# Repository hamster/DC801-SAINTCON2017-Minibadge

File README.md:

# DC801-SAINTCON2017-Minibadge
Minibadge design for the 2017 SAINTCON badge with a DC801 theme

Powered

Front

Back

The Minibadge includes a spiffy DC801 design and two automatic slow-cycling RGB LEDs

The Minibadge can be used in two ways:

1. SAINTCON Minibadge Mode
2. Shirt Pin Mode

# Instructions for SAINTCON Minibadge Mode

1) Insert the LEDs into the back of the board with the shorter legs toward the top
2) Bend the legs of the LEDs over to contact the pads
3) Trim legs to pads and solder
4) Pick a resistor and solder R1:
   0 - Brightest, 20-55mA
   470 - Bright, 3-4mA
   1k - Not so bright, 1.5-2mA
5) Break the pin headers to fit 
6) Cut the sockets into two 8 pin sockets 
7) Insert the sockets with pins into your SAINTCON badge
8) Place the DC801 Minibadge onto the pins and solder
9) Flip your SAINTCON badge over and solder on the sockets

# Instructions for Shirt Pin Mode

1) Follow above, but don’t use the pin headers
2) Solder included button pin to large pad at top

# BOM

Prices/sourcing as of 10/2017
Part prices do not include shipping costs - typical was about another $0.30 per unit

Item | Part Number | Sourcing | Cost Each (100 unit pricing) | Needed per kit | Total
-----|-------------|----------|------------------------------|----------------|------
PCB | 100 qty, black silkscreen | [seeed](https://www.seeedstudio.com/fusion_pcb.html) | $0.334 | 1 | $0.334
D1,2 | Chanzon AA0018x100 3mm LED | [Amazon](https://www.amazon.com/gp/product/B01C19ENH8) | $0.075 | 2 | $0.15
R1 | Yageo RC1206JR-070RL 0 Ohm | [Mouser](http://www.mouser.com/Search/ProductDetail.aspx?R=RC1206JR-070RL) | $0.006 | 1 | $0.006
R1 | Yageo RC1206FR-07470RL 470 Ohm | [Mouser](http://www.mouser.com/Search/ProductDetail.aspx?R=RC1206FR-07470RL) | $0.009 | 1 | $0.009
R1 | Yageo RC1206FR-071KL 1k Ohm | [Mouser](http://www.mouser.com/Search/ProductDetail.aspx?R=RC1206FR-071KL) | $0.009 | 1 | $0.009
Pins/Sockets | Pins and Sockets, 40 pin | [Amazon](https://www.amazon.com/gp/product/B074HVBTZ4) | $0.26 | 1/2 | $0.13
Shirt pins | Mudder Butterfly Clutch Tie Tacks | [Amazon](https://www.amazon.com/gp/product/B06VXNN1HK) | $0.0699 | 1 | $0.0699
Bags | Metallic foil clear/black | [Amazon](https://www.amazon.com/gp/product/B01DMG9BQW) | $0.1849 | 1 | $0.1849
Cards | Instruction Cards (500 qty) | Vistaprint | $0.01998 | 1 | $0.01998
Total | Per each board kit | | | | $0.913

# Battery Holder

Included in the [Shirt Pin Battery](/Shirt%20Pin%20Battery) folder is a board that can hold a battery to power the badge and attach to your shirt, if you want blinkies in a tiny package.

Hope you enjoy!

@hamster

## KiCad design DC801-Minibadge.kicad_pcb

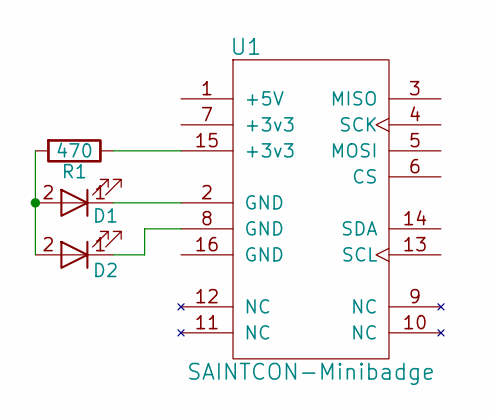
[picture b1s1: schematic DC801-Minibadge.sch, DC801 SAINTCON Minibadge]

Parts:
D1: LED; LED-3.0mm-ThroughBoard
D2: LED; LED-3.0mm-ThroughBoard-Flip
R1: 470; R_1206_HandSoldering
U1: SAINTCON-Minibadge; SAINTCON-Minibadge-NoSPI-NoSilk

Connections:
unnamed: D1.1 (K), U1.2 (GND)
unnamed: D1.2 (A), D2.2 (A), R1.2
unnamed: D2.1 (K), U1.8 (GND)
unnamed: R1.1, U1.15 (+3v3)

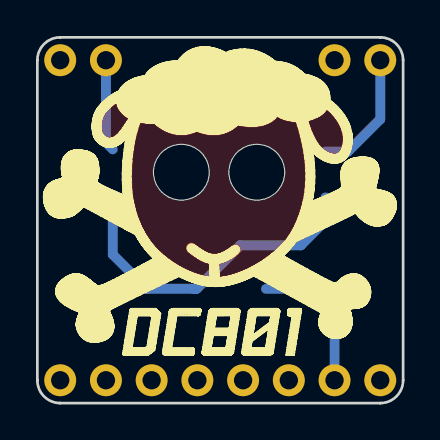
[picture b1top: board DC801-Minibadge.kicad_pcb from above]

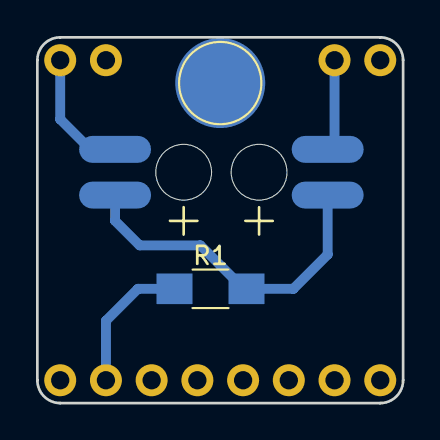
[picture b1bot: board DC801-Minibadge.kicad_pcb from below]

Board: 2 copper layers, 20.3 x 20.3 mm, 4 parts (3 on the bottom side), 4 nets.

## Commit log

2017-09-19 Adding design files
2017-09-22 Updating text on instruction card
2017-09-24 Add BOM
2017-09-24 Fix links in BOM
2017-09-24 Add shipping estimate to BOM
2017-09-24 Update the qty needed per board to correct the per-board price in BOM
2017-09-24 Updating pin/socket calculation to account for lose when trimming
2017-09-25 Moved the badge to a subdir
2017-09-26 Adding battery holder Adding actual images
2017-09-26 Fixing images
2017-09-26 Adding mentions of the shirt pin battery
